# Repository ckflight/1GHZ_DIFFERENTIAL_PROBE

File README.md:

# 1GHZ DIFFERENTIAL PROBE

Instead of paying a few thousand $ to the unnecessarily expensive probes from tektronix or rigol for daily use, i made a Differential Probe which cost
15$ for 4 layer pcb and 45$ for components and it works just fine.

Mosfet source follower is used as voltage buffer which has 20dB attenuation (1/10) and an opamp subtractor is used at the end. Copper pour at the input of the pcb is removed to reduce input capacitance of the probe for high speed signals. 2 passive LPF is used at the output of Switching Regulator which is generating ripple noise. Also input power from the USB Connector is filtered with 180 Ohm Ferrite Bead which is the input of the Switching Regulator. This way of filtering
is the best way of reducing ripple noise and switching peaks of the regulator. However using second LDO Regulator to filter out instead of using switching regulator is the best option for power filtering which means better high speed signal performance.

Design needs usb input power for powering the circuit and 50 Ohm SMA connector
is used. BNC 50 Ohm feedthrough connector can be used for connection to Oscilloscope if it does not have 50 Ohm option.

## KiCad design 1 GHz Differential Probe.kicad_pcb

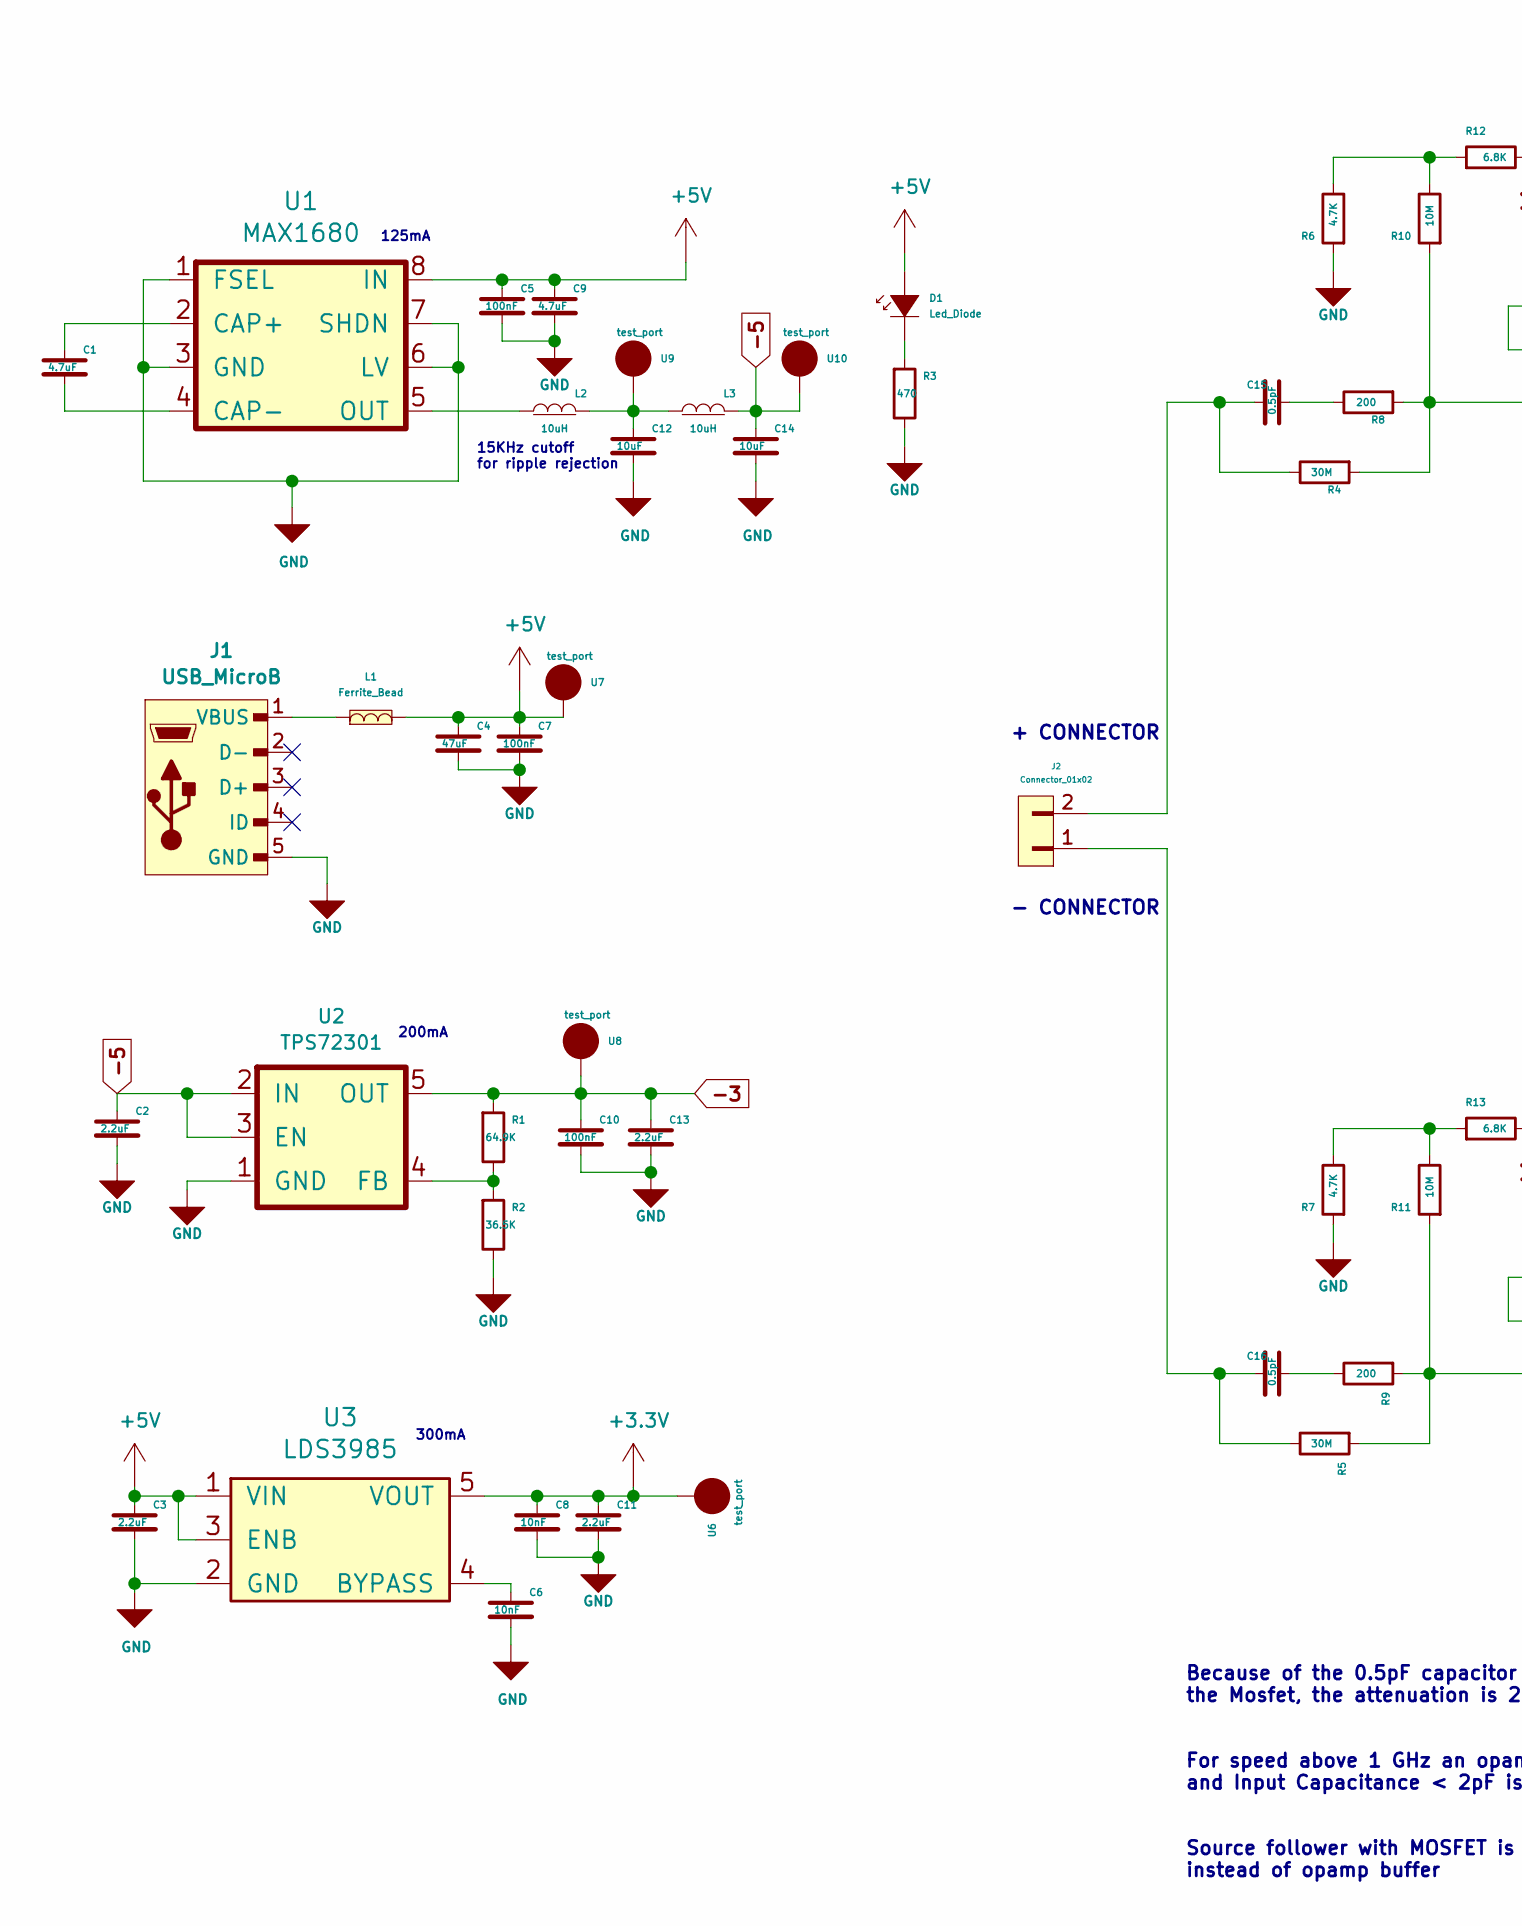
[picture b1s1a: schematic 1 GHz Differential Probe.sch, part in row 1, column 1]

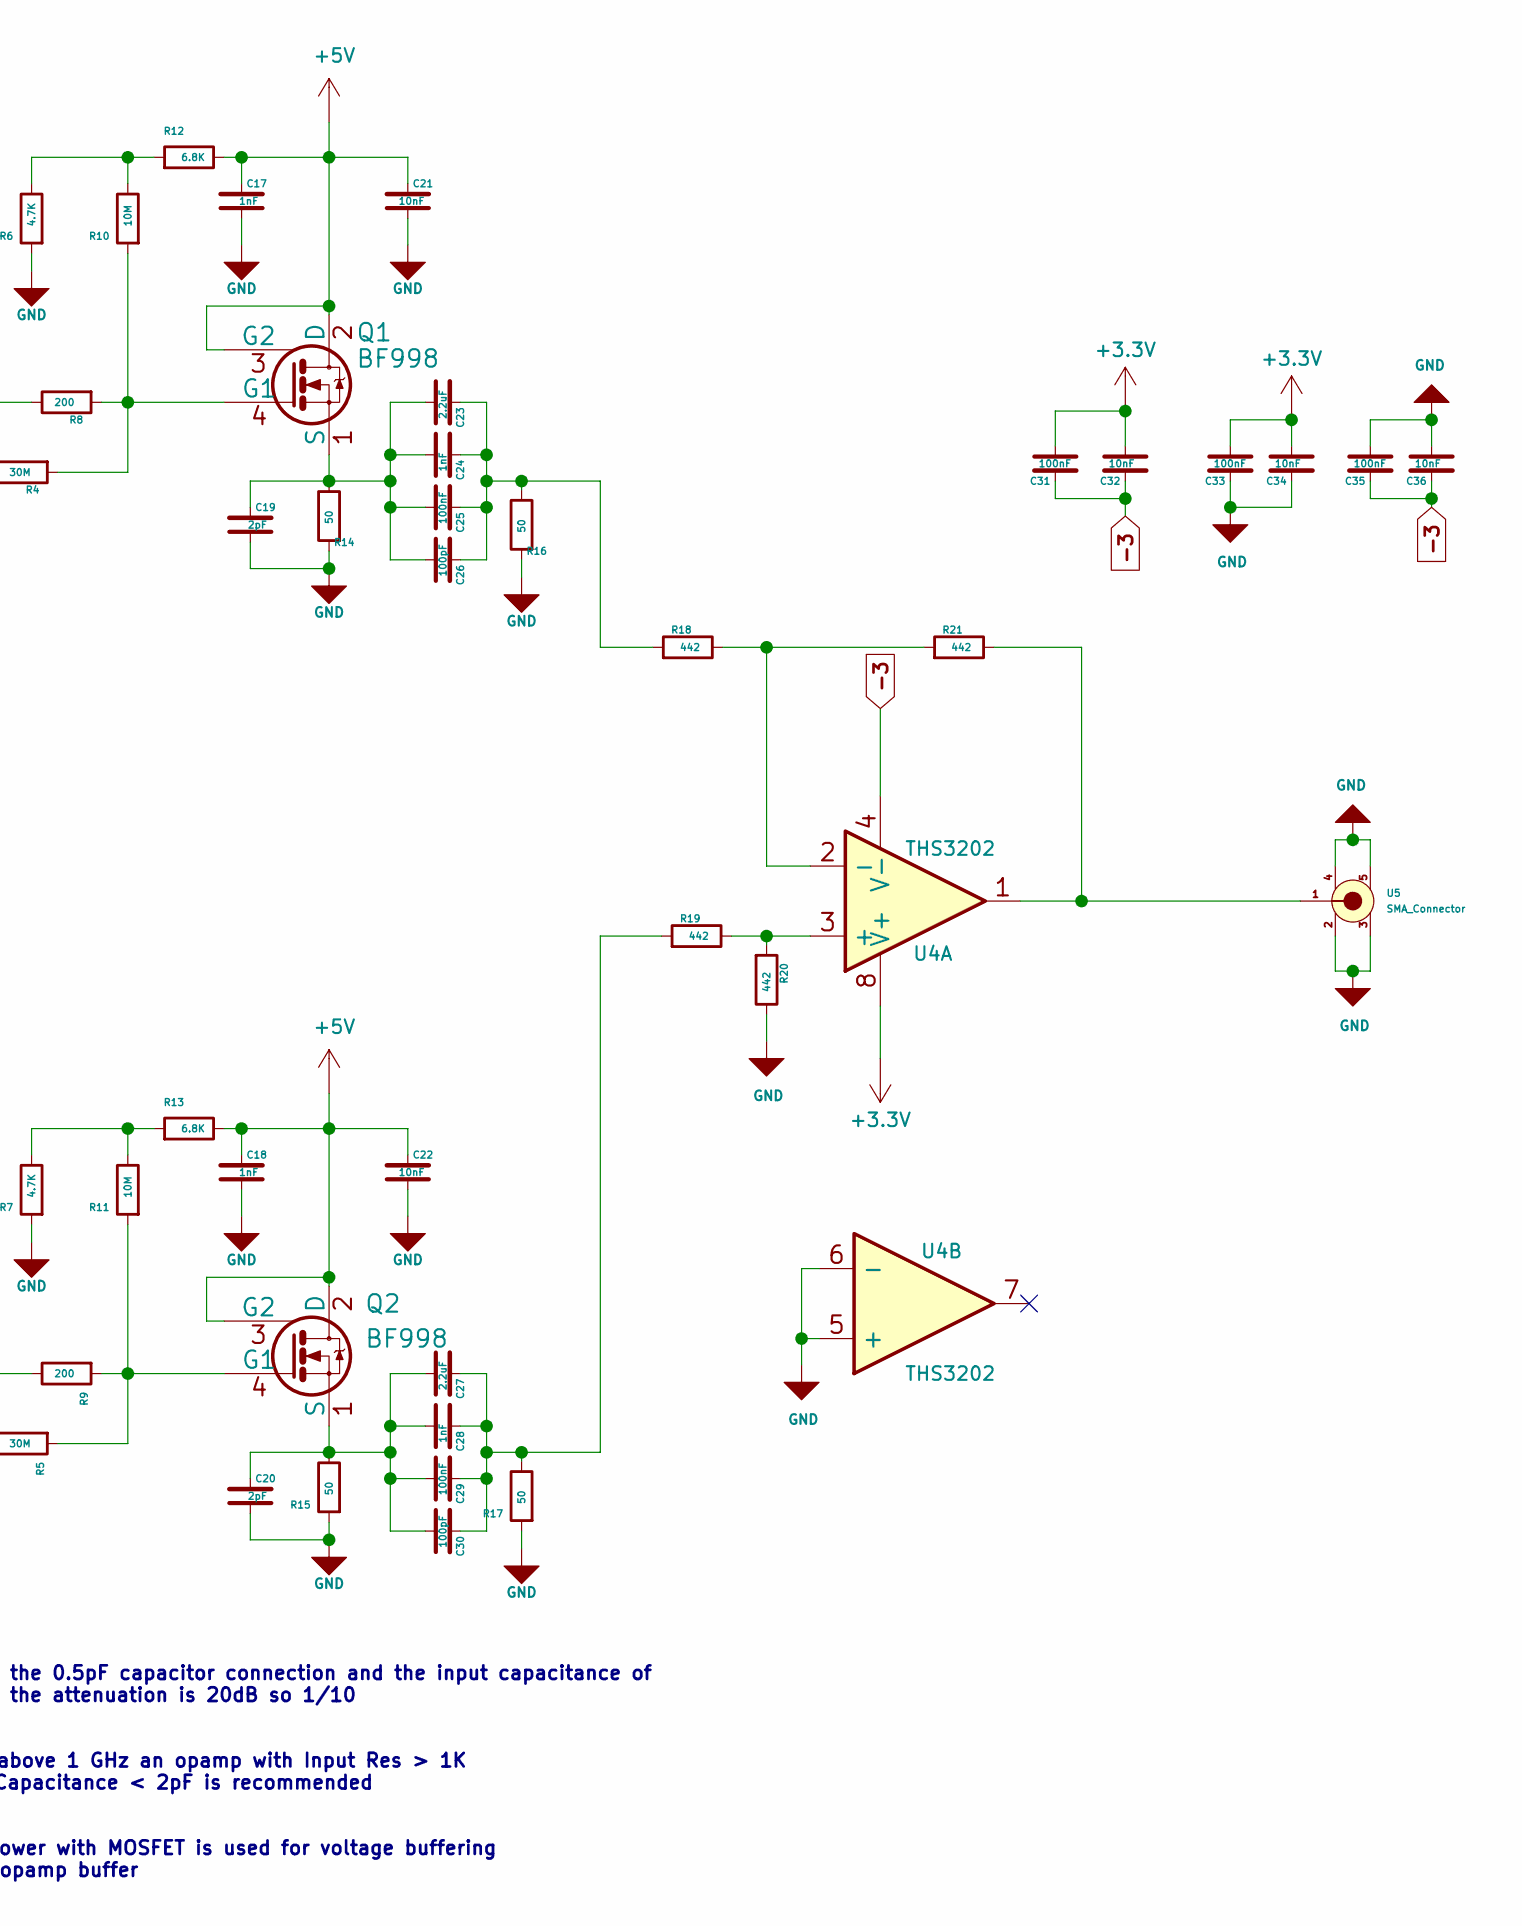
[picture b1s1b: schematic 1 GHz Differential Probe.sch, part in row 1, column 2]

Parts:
C1, C9: 4.7uF; SMD_0603
C2, C3, C11, C13, C23, C27: 2.2uF; SMD_0402
C4: 47uF; SMD_0805
C5, C7, C10, C25, C29, C31, C33, C35: 100nF; SMD_0402
C6, C8, C21, C22, C32, C34, C36: 10nF; SMD_0402
C12, C14: 10uF; SMD_0603
C15, C16: 0.5pF; SMD_0402
C17, C18, C24, C28: 1nF; SMD_0402
C19, C20: 2pF; SMD_0402
C26, C30: 100pF; SMD_0402
D1: Led_Diode; Diode_0603
J1: USB_MicroB; USB_MicroB_TH
J2: Connector_01x02; PinHeader_1x2_P2.5mm
L1: Ferrite_Bead; SMD_0805
L2, L3: 10uH; SMD_0805
Q1, Q2: BF998; SOT143
R1: 64.9K; SMD_0402
R2: 36.5K; SMD_0402
R3: 470; SMD_0402
R4, R5: 30M; SMD_0805
R6, R7: 4.7K; SMD_0402
R8, R9: 200; SMD_0402
R10, R11: 10M; SMD_0603
R12, R13: 6.8K; SMD_0402
R14, R15, R16, R17: 50; SMD_0402
R18, R19, R20, R21: 442; SMD_0402
U1: MAX1680; SO8_3.9X4.9mm_P1.27mm
U2: TPS72301; SOT23_5
U3: LDS3985; SOT23_5
U4: THS3202; VSSOP_8_3x3mm_P0.65mm
U5: SMA_Connector
U6, U7, U8, U9, U10: test_port; SolderPad_1_1.2mm_SMD_Circle

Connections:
+3V3: C8.1, C11.1, C31.1, C32.1, C33.1, C34.1, U3.5 (VOUT), U4.8 (V+), U6.1
+5V: C3.1, C4.1, C5.1, C7.1, C9.1, C17.2, C18.2, C21.2, C22.2, D1.2 (A), L1.2, Q1.2 (D), Q1.3 (G2), Q2.2 (D), Q2.3 (G2), R12.2, R13.2, U1.8 (IN), U3.1 (VIN), U3.3 (ENB), U7.1
-3: C10.1, C13.1, C31.2, C32.2, C35.2, C36.2, R1.1, U2.5 (OUT), U4.4 (V-), U8.1
-5: C2.1, C14.1, L3.2, U2.2 (IN), U2.3 (EN), U10.1
GND: C2.2, C3.2, C4.2, C5.2, C6.2, C7.2, C8.2, C9.2, C10.2, C11.2, C12.2, C13.2, C14.2, C17.1, C18.1, C19.1, C20.1, C21.1, C22.1, C33.2, C34.2, C35.1, C36.1, J1.5 (GND), R2.2, R3.2, R6.1, R7.1, R14.1, R15.1, R16.1, R17.1, R20.2, U1.1 (FSEL), U1.3 (GND), U1.6 (LV), U1.7 (SHDN), U2.1 (GND), U3.2 (GND), U4.5 (+), U4.6 (-), U5.2, U5.3, U5.4, U5.5
unnamed: C1.1, U1.2 (CAP+)
unnamed: C1.2, U1.4 (CAP-)
unnamed: C6.1, U3.4 (BYPASS)
unnamed: C12.1, L2.2, L3.1, U9.1
unnamed: C15.1, R8.2
unnamed: C15.2, J2.2, R4.2
unnamed: C16.1, R9.2
unnamed: C16.2, J2.1, R5.2
unnamed: C19.2, C23.1, C24.1, C25.1, C26.1, Q1.1 (S), R14.2
unnamed: C20.2, C27.1, C28.1, C29.1, C30.1, Q2.1 (S), R15.2
unnamed: C23.2, C24.2, C25.2, C26.2, R16.2, R18.1
unnamed: C27.2, C28.2, C29.2, C30.2, R17.2, R19.1
unnamed: D1.1 (K), R3.1
unnamed: J1.1 (VBUS), L1.1
unnamed: L2.1, U1.5 (OUT)
unnamed: Q1.4 (G1), R4.1, R8.1, R10.1
unnamed: Q2.4 (G1), R5.1, R9.1, R11.1
unnamed: R1.2, R2.1, U2.4 (FB)
unnamed: R6.2, R10.2, R12.1
unnamed: R7.2, R11.2, R13.1
unnamed: R18.2, R21.1, U4.2 (-)
unnamed: R19.2, R20.1, U4.3 (+)
unnamed: R21.2, U4.1, U5.1

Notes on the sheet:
+ CONNECTOR
- CONNECTOR
Because of the 0.5pF capacitor connection and the input capacitance of the Mosfet, the attenuation is 20dB so 1/10
For speed above 1 GHz an opamp with Input Res > 1K and Input Capacitance < 2pF is recommended
15KHz cutoff for ripple rejection
125mA
Source follower with MOSFET is used for voltage buffering instead of opamp buffer
200mA
300mA

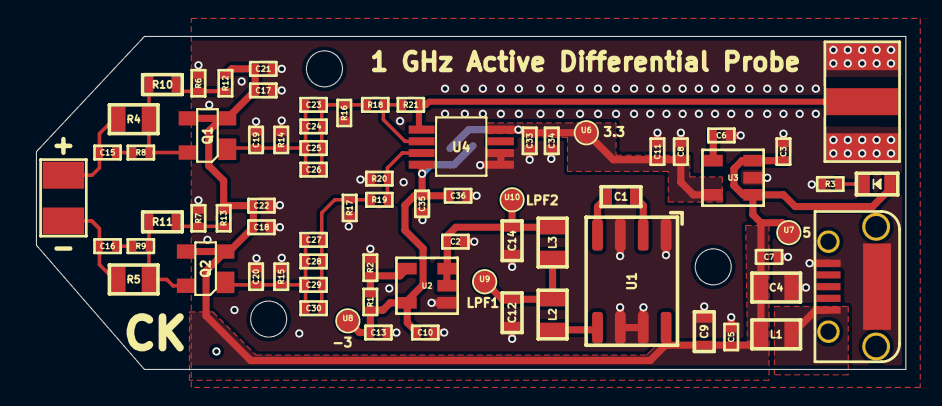
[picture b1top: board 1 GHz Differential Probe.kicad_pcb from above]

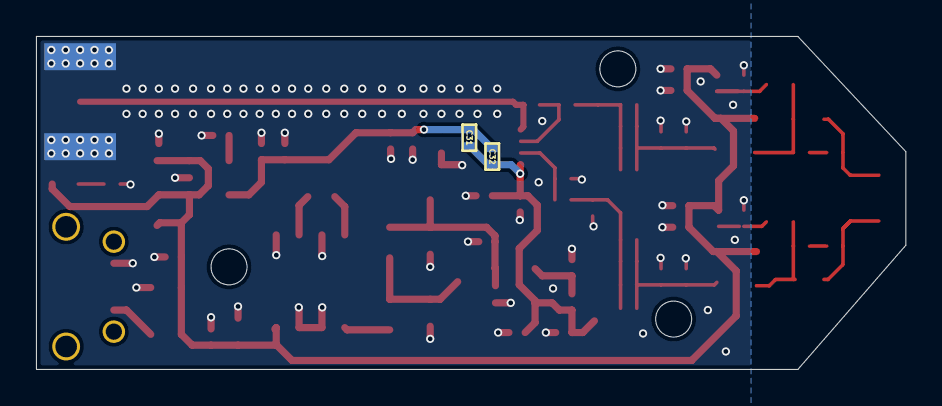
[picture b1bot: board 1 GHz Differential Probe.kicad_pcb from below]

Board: 4 copper layers, 48.3 x 18.5 mm, 75 parts (2 on the bottom side), 28 nets.
